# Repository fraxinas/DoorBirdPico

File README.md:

# DoorBirdPico

(CC) 2021 by Andreas Frisch <fraxinas@purplegecko.de>

## OwO what's this?

**`DoorBirdPico` is a custom Raspberry Pi Pico PCB design and code to add functionality to the DoorBird Voip entryphone.**

## Hardware Features

- ports for 3 RGB-lit doorbell buttons
- ports for 2 reed sensors (door/letterbox)
- hardware debouncing
- power / UART communication with Doorbird D2100E
- 2 input ports for the Doorbird relays
- 1 potential-free relay output (for door opener)
- RS485 transceiver

## Software

- using Rasperry Pi Pico C API
- interrupt services routines for buttons
- color-fading PWM

## Project Diary

| Date       | Version | Milestone                                       |
| :--------- | :------ | :---------------------------------------------- |
| 2021-04-06 |         | Pico on Breadboard, pushbutton irq & pwm        |
| 2021-04-13 |         | Implemented UART communication with Doorbird    |
| 2021-04-16 |         | Started git repository                          |
| 2021-05-12 | v0.1    | Commission of 1st prototype PCB with aisler.net |
| 2021-06-02 | v0.1    | Received prototype PCB                          |
| 2021-06-04 | v0.1    | Assembling of prototype PCB                     |
| 2021-06-06 | v0.2    | Software is essentially ready                   |

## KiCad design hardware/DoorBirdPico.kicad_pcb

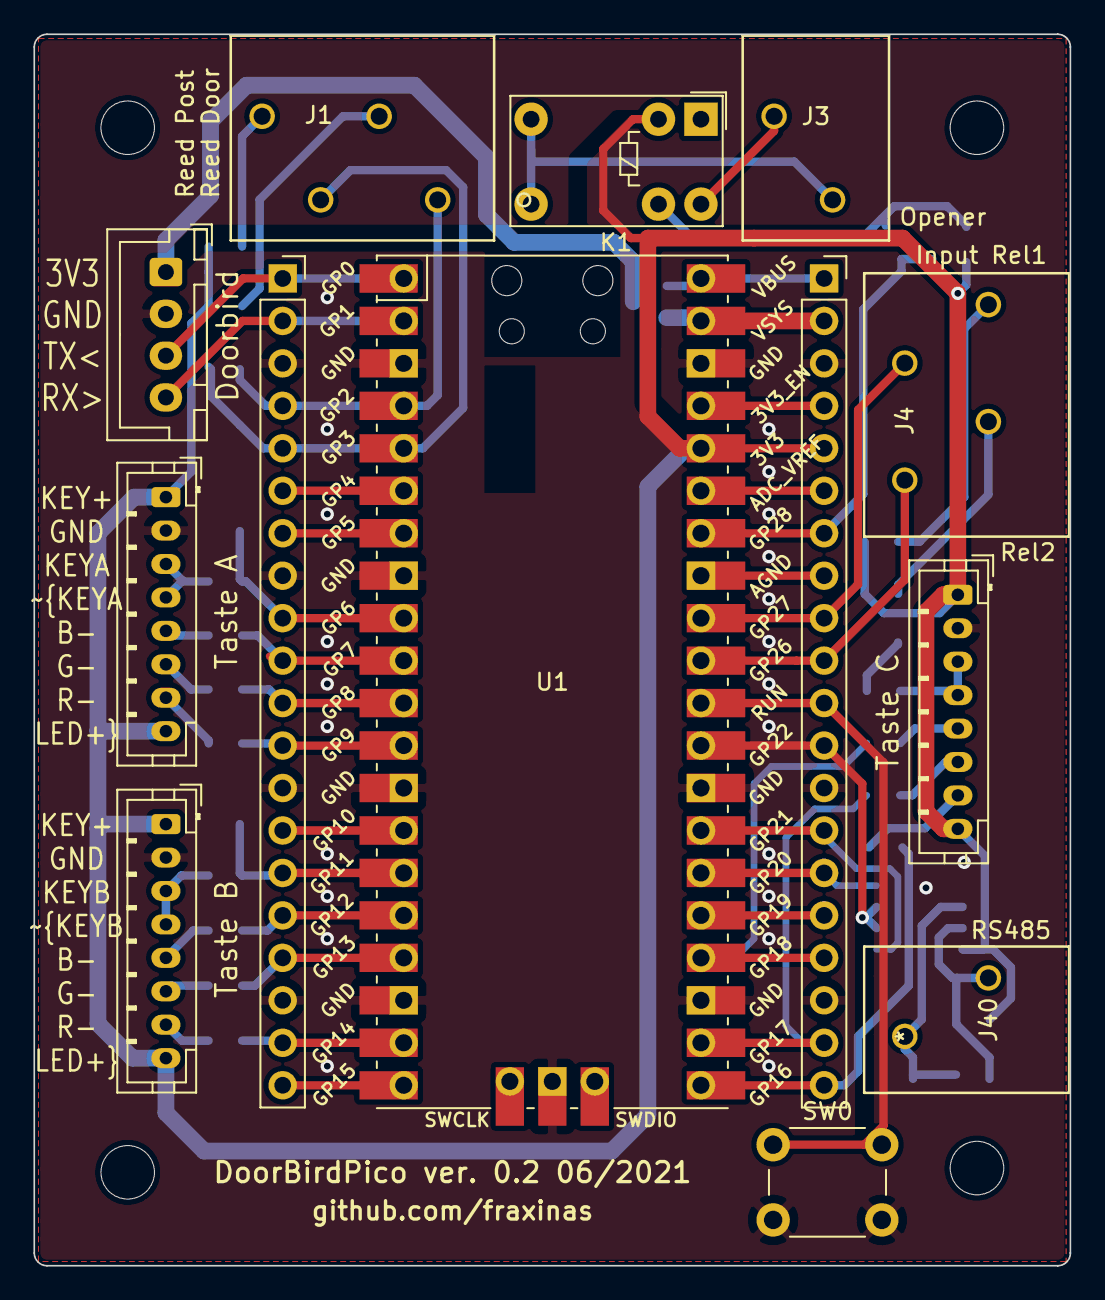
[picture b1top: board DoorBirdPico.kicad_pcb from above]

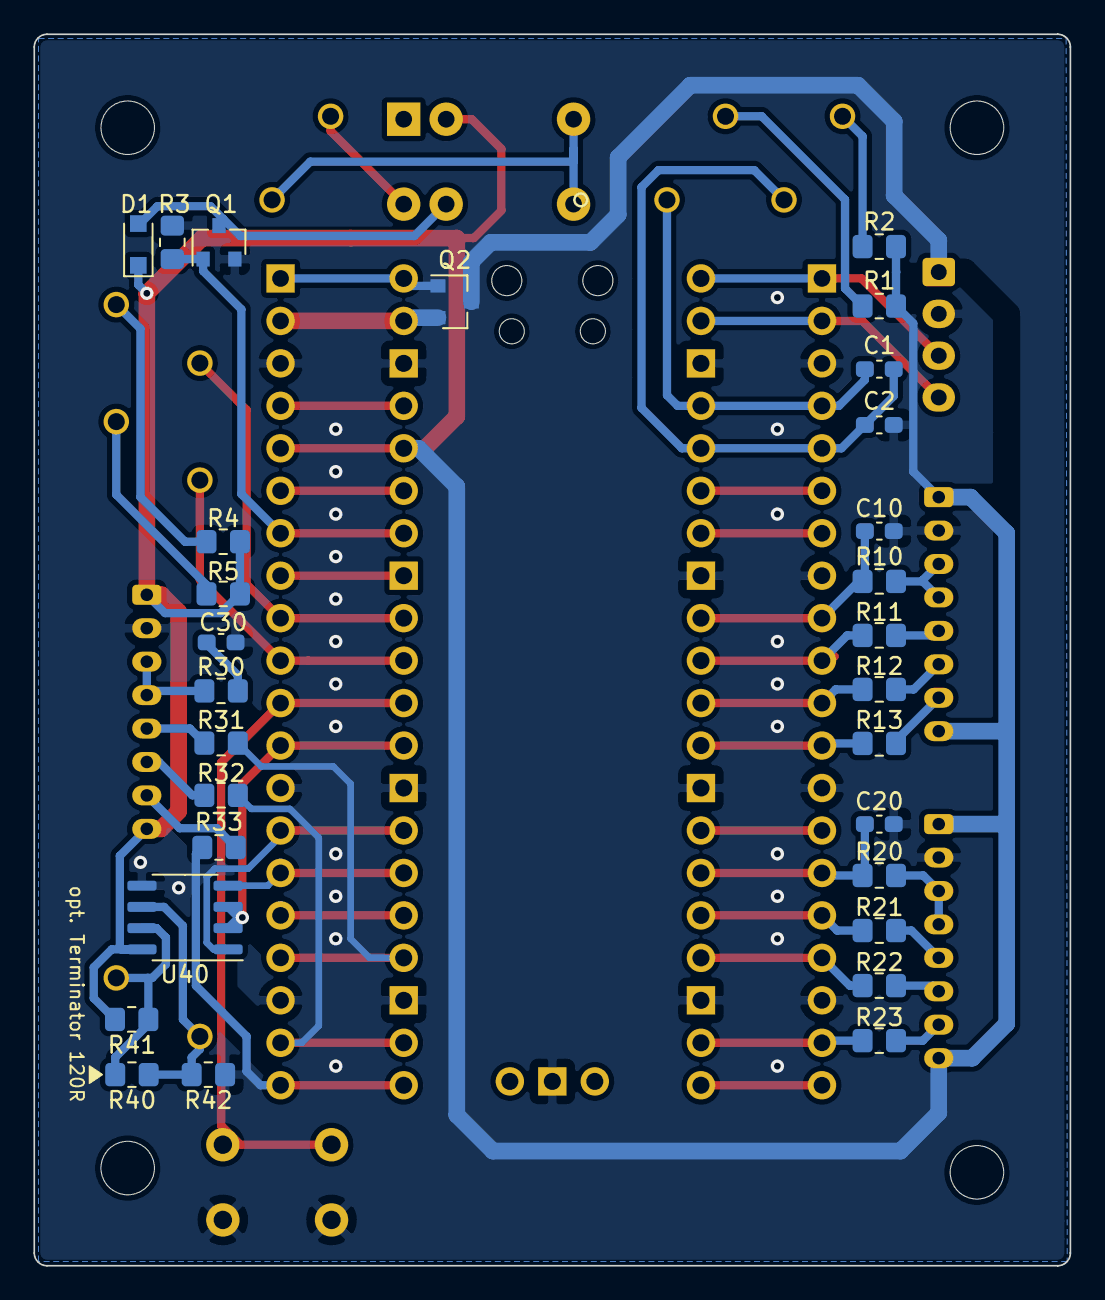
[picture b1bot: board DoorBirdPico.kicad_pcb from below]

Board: 2 copper layers, 62.0 x 73.7 mm, 42 parts (29 on the bottom side), 57 nets.

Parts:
C1, C2, C10, C20, C30: 22nF; C_0603_1608Metric_Pad1.08x0.95mm_HandSolder
D1: 1N4148WS; D_SOD-323_HandSoldering
J0: Doorbird; JST_XH_B4B-XH-A_1x04_P2.50mm_Vertical
J1: Reed; 250-204
J3: Relay_Opener; 250-202
J4: Relais_in; 250-204
J10: Taste A; JST_PH_B8B-PH-K_1x08_P2.00mm_Vertical
J20: Taste B; JST_PH_B8B-PH-K_1x08_P2.00mm_Vertical
J30: Taste C; JST_PH_B8B-PH-K_1x08_P2.00mm_Vertical
J40: RS485; 250-202
J98, J99: Conn_01x20; PinSocket_1x20_P2.54mm_Vertical
K1: G5V-1; Relay_SPDT_Omron_G5V-1
Q1: AO3400A; SOT-23
Q2: AO3401A; SOT-23
R1, R2, R4, R5: 100R; R_0805_2012Metric_Pad1.20x1.40mm_HandSolder
R3: 68k; R_0805_2012Metric_Pad1.20x1.40mm_HandSolder
R10, R20, R30, R41, R42: 12k; R_0805_2012Metric_Pad1.20x1.40mm_HandSolder
R11, R21, R31: 22R; R_0805_2012Metric_Pad1.20x1.40mm_HandSolder
R12, R22, R32: 68R; R_0805_2012Metric_Pad1.20x1.40mm_HandSolder
R13, R23, R33: 82R; R_0805_2012Metric_Pad1.20x1.40mm_HandSolder
R40: 120; R_0805_2012Metric_Pad1.20x1.40mm_HandSolder
SW0: SW_Push; SW_PUSH_6mm_H5mm
U1: PICO_RP2040; RPi_Pico_SMD_TH
U40: MAX3485; SO-8_3.9x4.9mm_P1.27mm

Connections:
+3V3: D1.1, J10.1, J10.8, J20.1, J20.8, J30.1, J30.8, J98.5, K1.2, R1.1, R2.1, R4.2, R5.2, R41.1, U1.36, U40.8
GND: C2.2, C10.1, C20.1, J0.2, J10.2, J20.2, J30.2, J98.3, J98.13, J98.18, J99.3, J99.8, J99.13, J99.18, Q1.2, R3.2, R42.2, SW0.2, U1.3, U1.8, U1.13, U1.18, U1.23, U1.28, U1.38, U1.42, U40.5
unnamed: C1.1, J1.1, J99.4, U1.4
unnamed: C1.2, C2.1, J1.3, J99.5, U1.5
unnamed: C10.2, J99.9, R10.1, U1.9
unnamed: C20.2, J99.15, R20.1, U1.15
unnamed: C30.2, R30.1
unnamed: D1.2, K1.9, Q1.3
unnamed: J0.1, Q2.3
unnamed: J0.3, J99.1, U1.1
unnamed: J0.4, J99.2, U1.2
unnamed: J1.2, R1.2
unnamed: J1.4, R2.2
unnamed: J3.1, K1.5, K1.6
unnamed: J3.2, K1.10
unnamed: J4.1, J98.10, U1.31
unnamed: J4.2, R5.1
unnamed: J4.3, J98.9, U1.32
unnamed: J4.4, R4.1
unnamed: J10.3, J10.4, R10.2
unnamed: J10.5, R11.1
unnamed: J10.6, R12.1
unnamed: J10.7, R13.1
unnamed: J20.3, J20.4, R20.2
unnamed: J20.5, R21.1
unnamed: J20.6, R22.1
unnamed: J20.7, R23.1
unnamed: J30.3, J30.4, R30.2
unnamed: J30.5, R31.1
unnamed: J30.6, R32.1
unnamed: J30.7, R33.1
unnamed: J40.1, R40.2, R42.1, U40.6
unnamed: J40.2, R40.1, R41.2, U40.7
unnamed: J98.1, Q2.1, U1.40
unnamed: J98.2, Q2.2, U1.39
unnamed: J98.4, U1.37
unnamed: J98.6, U1.35
unnamed: J98.7, Q1.1, R3.1, U1.34
unnamed: J98.8, U1.33
unnamed: J98.11, SW0.1, U1.30
unnamed: J98.12, U1.29, U40.2, U40.3
unnamed: J98.14, U1.27, U40.1
unnamed: J98.15, U1.26, U40.4
unnamed: J98.16, U1.25
unnamed: J98.17, R31.2, U1.24
unnamed: J98.19, R32.2, U1.22
unnamed: J98.20, R33.2, U1.21
unnamed: J99.6, U1.6
unnamed: J99.7, U1.7
unnamed: J99.10, R11.2, U1.10
unnamed: J99.11, R12.2, U1.11
unnamed: J99.12, R13.2, U1.12
unnamed: J99.14, U1.14
unnamed: J99.16, R21.2, U1.16
unnamed: J99.17, R22.2, U1.17
unnamed: J99.19, R23.2, U1.19
unnamed: J99.20, U1.20

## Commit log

2021-04-16 Readme: Add initial description
2021-04-16 hardware: Add initial KiCAD project, schematic & PCB
2021-04-16 Schema: Add 3rd RGB button port, 2 relay inputs, 1 relay output
2021-04-17 Schema: Add MAX3485 Transceiver
2021-04-17 hardware: Fix lib table
2021-04-17 PCB: Add RS485 components
2021-05-18 Hardware: Add RS485 circuitry resistors
2021-05-19 Add .gitignore
2021-05-19 Library: Add symbols + footprints for WAGO 250 terminals
2021-05-19 Library: Move footprints into subdir
2021-05-19 Hardware: Use WAGO 250 Terminals in Schema & PCB
2021-05-19 Hardware: Get ready for production
    * Silkscreen label placements
    * D1 handsolderable footprint
2021-05-19 Software: Add initial software, LED PWM on keypress
2021-05-19 Software: Implement 2nd Key, implement bidirectional UART
2021-05-21 sofware: Use cmake build automation
2021-05-21 Readme: Update diary and feature list
2021-05-21 Software: Add readme, document UART communication
2021-05-21 Software: Use correct Key/LED GPIOs
2021-05-21 Software: Add relay input and outputs
2021-05-21 Software: Add opening / locking / delayed locking from the inside key
2021-05-26 Software: Fix & Improve sensor_input function
2021-05-27 Software: use timers instead of sleeps for yellow light / leaving lock delay
2021-06-01 Schema: Add wire colors to Key connector
2021-06-02 Software: Only use one interrupt service callback, fix typo
2021-06-03 Readme: Add TODO list for next rev.
2021-06-04 Software: Enable relay GPIOs and set relay and reed input pulldowns
2021-06-04 README: Move Todos from software to globale README, fix rev. in diary
2021-06-04 Software: Add blinking status LED
2021-06-05 Software: Initialize GPIOs properly, reverse color polarity
2021-06-05 Software: Indentation / Linting (no functional changes)
2021-06-05 Software: Add UART sendfunc, rename post->letter, fix lock/unlock key cb
    * DO NOT use sleep in ISR, it will freeze
2021-06-05 Software: Debounce digital inputs
2021-06-05 Readme: Add reset button to TODOs
2021-06-06 Software: improve edge debouncing / detection
2021-06-06 software: Add .vscode project settings
2021-06-06 software: Add .gitignores for src and build dir
2021-06-06 Software: Fix Key C long pressed detection, refactor color setter
2021-06-06 Schematic: Use 3V3 pin instead of Vsys
2021-06-06 Schematic: Fix C1
2021-06-06 Schematic: Fix R1, R2, R4, R5 values
2021-06-06 Readme: Update Project diary
2021-06-07 Schematic: Add reset switch
2021-06-07 Software: Refactoring of lock event ISR/CBs, debug strings
2021-06-08 Software: Implement 16 bit gamma LUT for LED PWM
2021-06-08 Software: refactor key PWM (WIP)
    * this freezes in the pwm_wrap function
2021-06-09 Software: Refactor key LED PWM (WIP)
2021-06-09 Software: Work on PWM handling, fix re-triggering (WIP)
    * Concurrent keys pwm doesn't work properly yet
2021-06-10 Software: Fix PWM slice handling
2021-06-10 Software: Implement start and end vals for PWM colors
    * works both ways around (up and down)
    * only works right if multiple Pins have same steps
2021-06-12 Software: Don't re-init PWM on 2nd keypress (workaround slow concurrent operation)
2021-06-13 PCB: Add Reset button, fix v0.2 TODOs
2021-06-14 Readme: Remove v0.2 TODOs
2021-06-16 Software: Separate includes, defines and declarations into header file
2021-06-16 Software: Add RS485 Receiver / Sender
2021-06-19 Software: Read & send RS485 commands
2021-06-20 Software: Improve RS485 message parsing and sending, add reed keys
2021-06-26 Software: Try to fix reading from RS485
2021-06-29 Software: Try workaround for UART1 init (WIP)
2021-06-30 Software: Use explicit timeout for RS485 UART RX
2021-07-01 Software: Fix handling RS485 commands
    * fix syntax in key string array definition
    * disable IRQ while processing RX, reenable afterwards
2021-07-01 Software: Fix RS485 RX command terminations
2021-07-01 Software: switch UART1 & UART0 between Doorbird and RS485
2021-07-03 Software: Add driver enable pin control for RS485
2021-07-03 Schematic: Bodge UART1 RS485 pins
2021-07-03 Software: Change UART Pins to the correct GPIOs
2021-07-04 Hardware: Plot bodged schematic
2021-07-05 Schematic: Add P-MOS for decoupling Doorbird VCC from USB Power
2021-07-05 PCB: Add P-MOS for decoupling Doorbird VCC from USB Power
2021-07-05 Hardware: Update KiCAD Project file
2021-07-06 Software: Clean up uart init function
2021-07-07 Software: Add COLOR setter command, implement brightness adjustment
    TODO: Concurrent fading, fix PWM init on same slices
2021-07-08 Software: Work on PWM fading (WIP)
2021-07-08 Software: Implement multicore processing of RS485 commands
2021-07-09 Software: use green / purple init colors again
2021-08-14 Software: Fix RS485 TX line endings
2021-08-14 Software: Fix double locking on short press, enable unlocking before buzzer
2021-08-22 Software: Filter out input pin glitch interrupts, ignore Key C release
2021-08-23 Software: Add safety watchdog timer for turning off buzzer

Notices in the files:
parts and their libraries:
Copyright 2016 Accelerated Designs. All rights reserved.
